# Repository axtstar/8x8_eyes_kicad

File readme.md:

# 8x8 eyes

マトリクスLED 1588BSの点灯用の基板設計

全て2.54mmピッチ

↓基板以外に必要なもの↓

* 1588BS
* 74HC595 x 2
* Registor(220Ω) x 8
* Capacitor(0.1uF) x 1
* 半田
* はんだごて

# 回路

# PCB

# 完成予想図

表

裏

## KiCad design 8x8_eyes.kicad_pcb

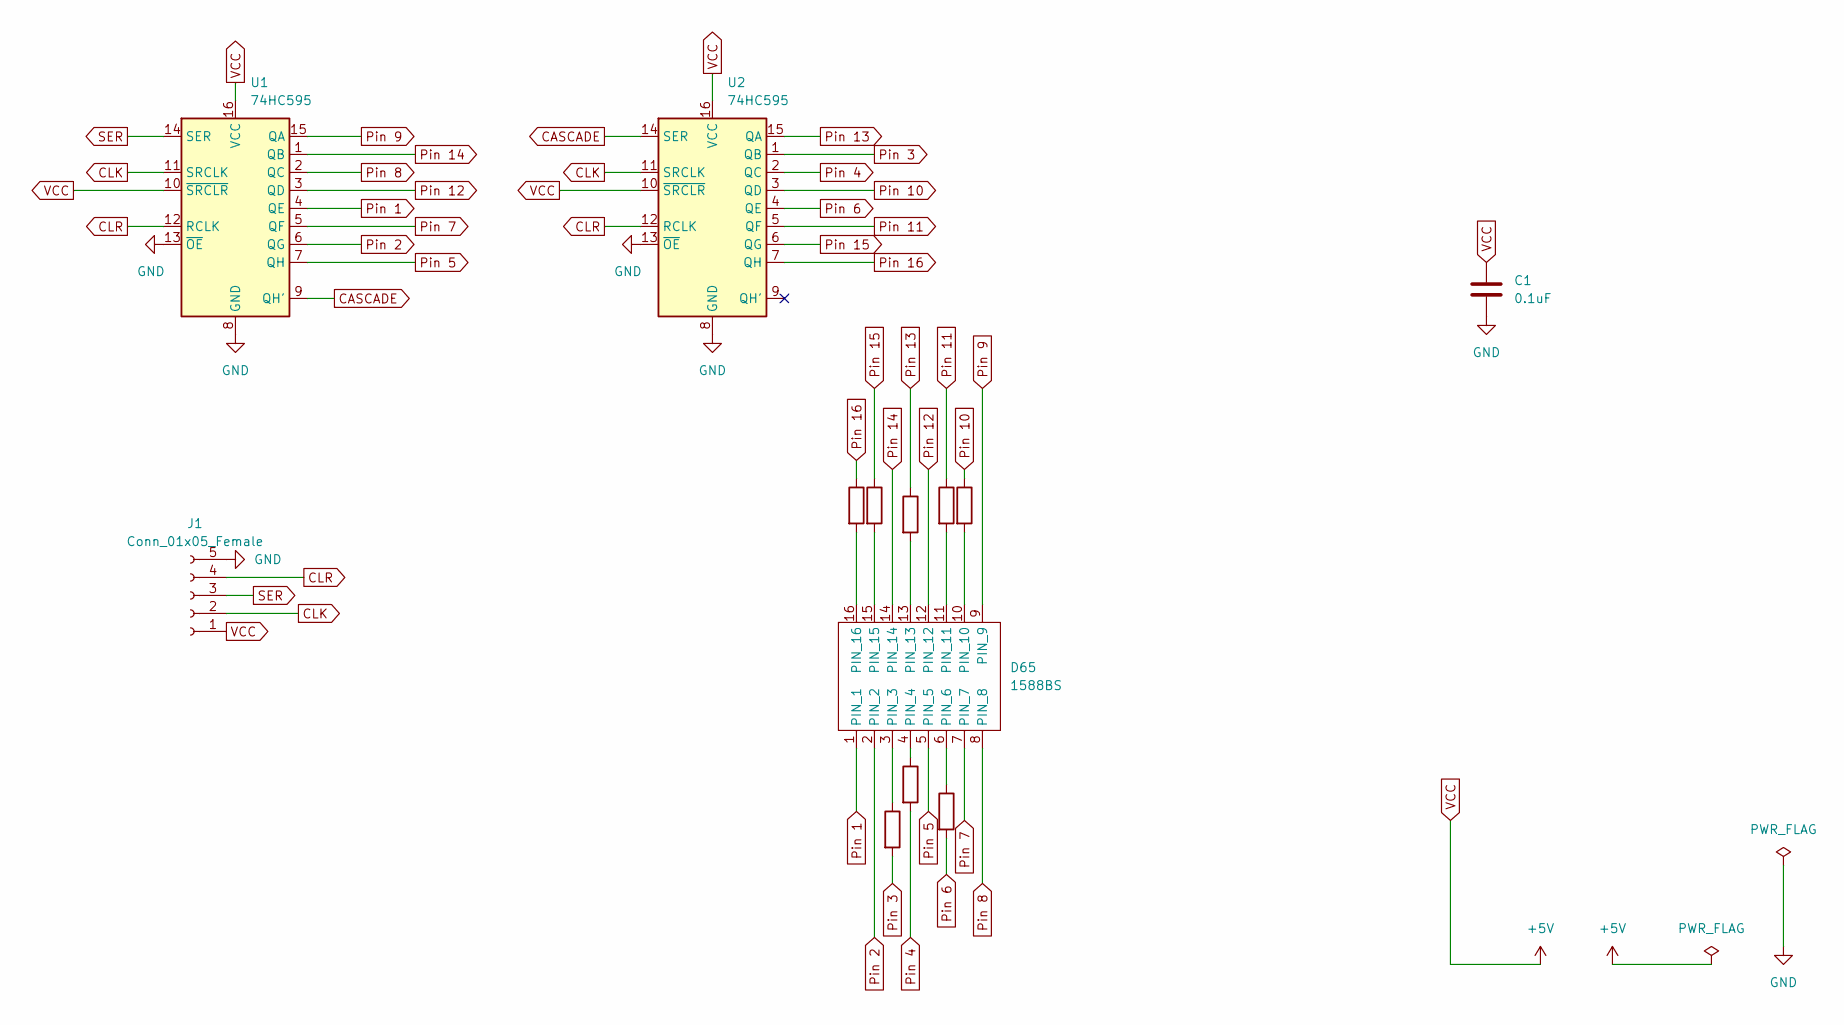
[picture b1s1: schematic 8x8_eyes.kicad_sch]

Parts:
C1: 0.1uF; C_Axial_L3.8mm_D2.6mm_P7.50mm_Horizontal
D65: 1588BS
J1: Conn_01x05_Female; Molex_KK-254_AE-6410-05A_1x05_P2.54mm_Vertical
R1, R2, R3, R4, R5, R6, R7, R8: 220; R_Axial_DIN0204_L3.6mm_D1.6mm_P5.08mm_Horizontal
U1, U2: 74HC595; DIP-16_W7.62mm

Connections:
CASCADE: U1.9 (QH'), U2.14 (SER)
CLK: J1.2, U1.11 (SRCLK), U2.11 (SRCLK)
CLR: J1.4, U1.12 (RCLK), U2.12 (RCLK)
GND: C1.2, J1.5, U1.8 (GND), U1.13 (~OE), U2.8 (GND), U2.13 (~OE)
unnamed: D65.3 (PIN), R2.1
unnamed: D65.4 (PIN), R4.1
unnamed: D65.6 (PIN), R3.1
unnamed: D65.10 (PIN), R5.2
unnamed: D65.11 (PIN), R6.2
unnamed: D65.13 (PIN), R1.2
unnamed: D65.15 (PIN), R7.2
unnamed: D65.16 (PIN), R8.2
Pin 1: D65.1 (PIN), U1.4 (QE)
Pin 2: D65.2 (PIN), U1.6 (QG)
Pin 3: R2.2, U2.1 (QB)
Pin 4: R4.2, U2.2 (QC)
Pin 5: D65.5 (PIN), U1.7 (QH)
Pin 6: R3.2, U2.4 (QE)
Pin 7: D65.7 (PIN), U1.5 (QF)
Pin 8: D65.8 (PIN), U1.2 (QC)
Pin 9: D65.9 (PIN), U1.15 (QA)
Pin 10: R5.1, U2.3 (QD)
Pin 11: R6.1, U2.5 (QF)
Pin 12: D65.12 (PIN), U1.3 (QD)
Pin 13: R1.1, U2.15 (QA)
Pin 14: D65.14 (PIN), U1.1 (QB)
Pin 15: R7.1, U2.6 (QG)
Pin 16: R8.1, U2.7 (QH)
SER: J1.3, U1.14 (SER)
VCC: C1.1, J1.1, U1.10 (~SRCLR), U1.16 (VCC), U2.10 (~SRCLR), U2.16 (VCC)

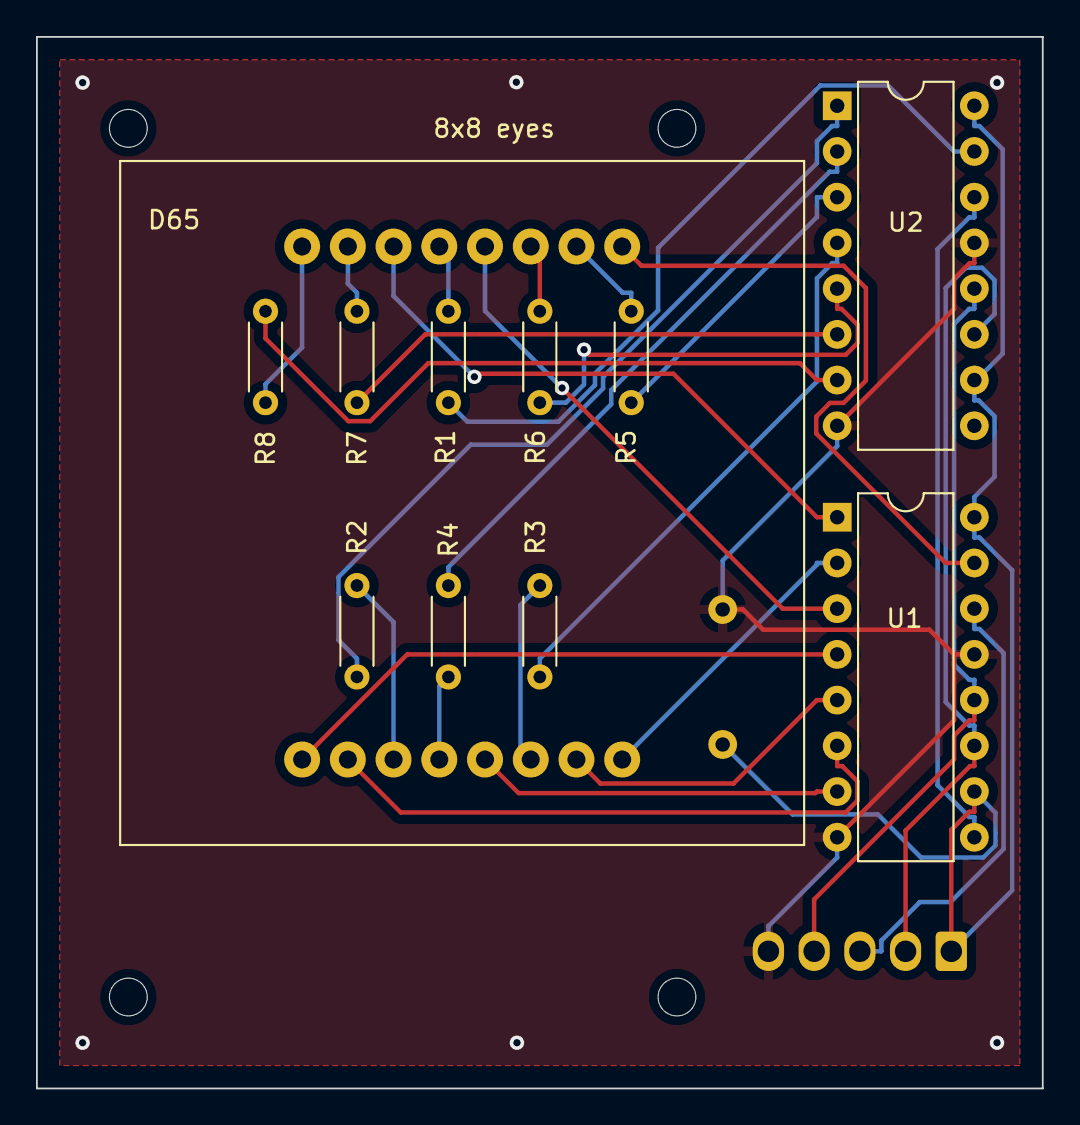
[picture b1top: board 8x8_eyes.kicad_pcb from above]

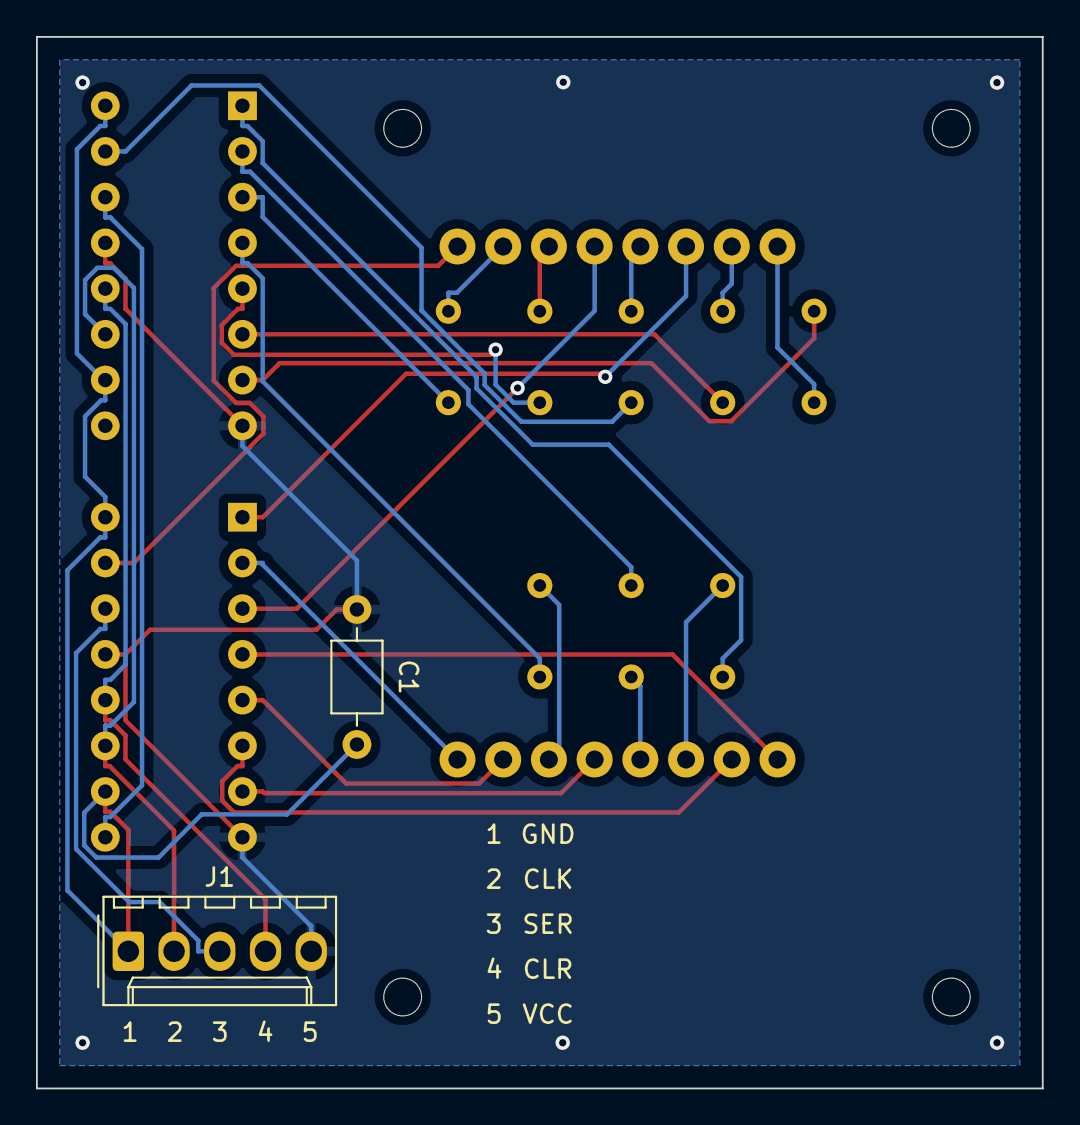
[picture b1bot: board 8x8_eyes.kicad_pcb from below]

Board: 2 copper layers, 55.9 x 58.4 mm, 13 parts (2 on the bottom side), 30 nets.

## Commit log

2022-02-20 remove gerber files and add plugin output dir ignore
2022-02-20 add readme
2025-04-13 update readme to enhance image descriptions and add missing images
